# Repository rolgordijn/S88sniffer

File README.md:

# S88NSniffer – Arduino + KiCad

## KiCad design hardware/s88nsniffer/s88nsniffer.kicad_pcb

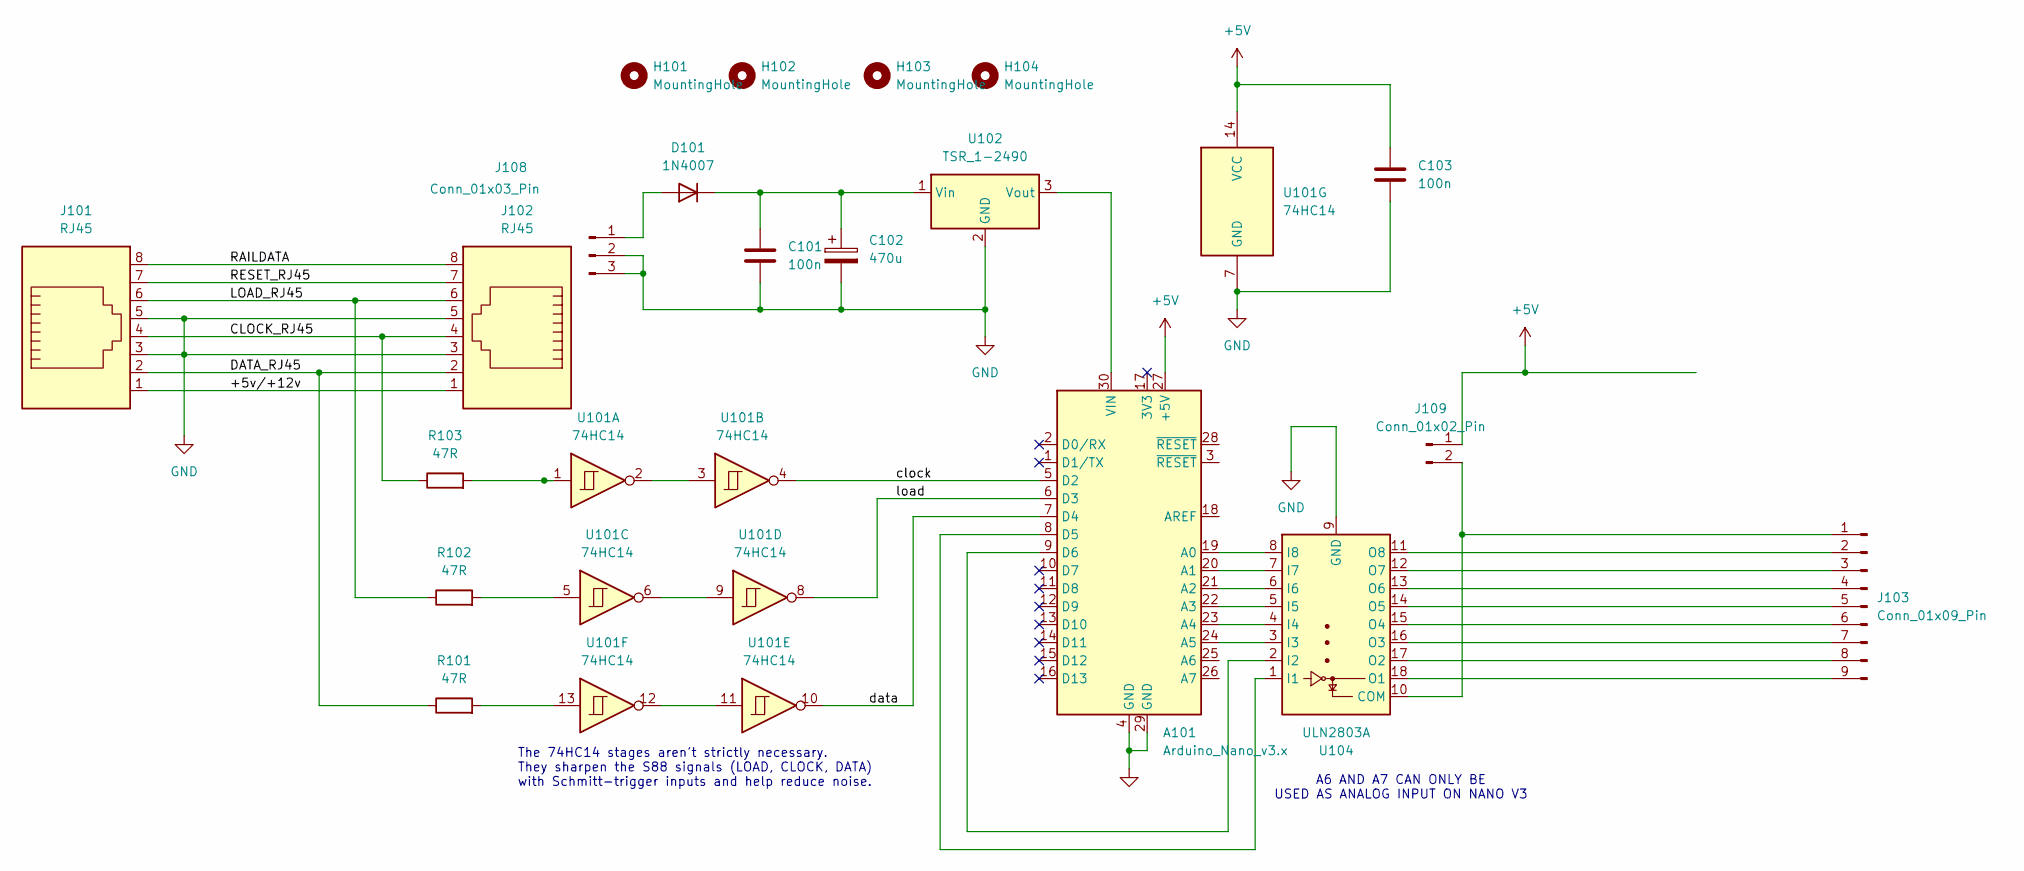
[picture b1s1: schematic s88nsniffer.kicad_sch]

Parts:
A101: Arduino_Nano_v3.x; Arduino_Nano
C101, C103: 100n; C_0805_2012Metric
C102: 470u; CP_Radial_D10.0mm_P3.50mm
D101: 1N4007; D_DO-41_SOD81_P10.16mm_Horizontal
H101, H102, H103, H104: MountingHole; MountingHole_4mm
J101, J102: RJ45; RJ45_Amphenol_RJHSE5380
J103: Conn_01x09_Pin; JST_PH_B9B-PH-K_1x09_P2.00mm_Vertical
J108: Conn_01x03_Pin; JST_PH_B3B-PH-K_1x03_P2.00mm_Vertical
J109: Conn_01x02_Pin; PinHeader_1x02_P2.54mm_Vertical
R101, R102, R103: 47R; C_0805_2012Metric
U101: 74HC14; DIP-14_W7.62mm
U102: TSR_1-2490; Converter_DCDC_TRACO_TSR-1_THT
U104: ULN2803A; DIP-18_W7.62mm

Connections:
+5V: A101.27 (+5V), C103.1, J109.1, U101.14 (VCC)
/+5v/+12v: J101.1, J102.1
/CLOCK_RJ45: J101.4, J102.4, R103.1
/DATA_RJ45: J101.2, J102.2, R101.1
/LOAD_RJ45: J101.6, J102.6, R102.1
/RAILDATA: J101.8, J102.8
/RESET_RJ45: J101.7, J102.7
/clock: A101.5 (D2), U101.4
/data: A101.7 (D4), U101.10
/load: A101.6 (D3), U101.8
GND: A101.4 (GND), A101.29 (GND), C101.2, C102.2, C103.2, J101.3, J101.5, J102.3, J102.5, J108.2, J108.3, U101.7 (GND), U102.2 (GND), U104.9 (GND)
unnamed: A101.19 (A0), U104.8 (I8)
unnamed: A101.20 (A1), U104.7 (I7)
unnamed: A101.21 (A2), U104.6 (I6)
unnamed: A101.22 (A3), U104.5 (I5)
unnamed: A101.23 (A4), U104.4 (I4)
unnamed: A101.24 (A5), U104.3 (I3)
unnamed: A101.8 (D5), U104.1 (I1)
unnamed: A101.9 (D6), U104.2 (I2)
unnamed: A101.30 (VIN), U102.3 (Vout)
unnamed: D101.2 (A), J108.1
unnamed: C101.1, C102.1, D101.1 (K), U102.1 (Vin)
unnamed: J103.1, J109.2, U104.10 (COM)
unnamed: J103.2, U104.11 (O8)
unnamed: J103.3, U104.12 (O7)
unnamed: J103.4, U104.13 (O6)
unnamed: J103.5, U104.14 (O5)
unnamed: J103.6, U104.15 (O4)
unnamed: J103.7, U104.16 (O3)
unnamed: J103.8, U104.17 (O2)
unnamed: J103.9, U104.18 (O1)
unnamed: R101.2, U101.13
unnamed: R102.2, U101.5
unnamed: R103.2, U101.1
unnamed: U101.2, U101.3
unnamed: U101.6, U101.9

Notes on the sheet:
The 74HC14 stages aren't strictly necessary. They sharpen the S88 signals (LOAD, CLOCK, DATA) with Schmitt-trigger inputs and help reduce noise.
A6 AND A7 CAN ONLY BE USED AS ANALOG INPUT ON NANO V3

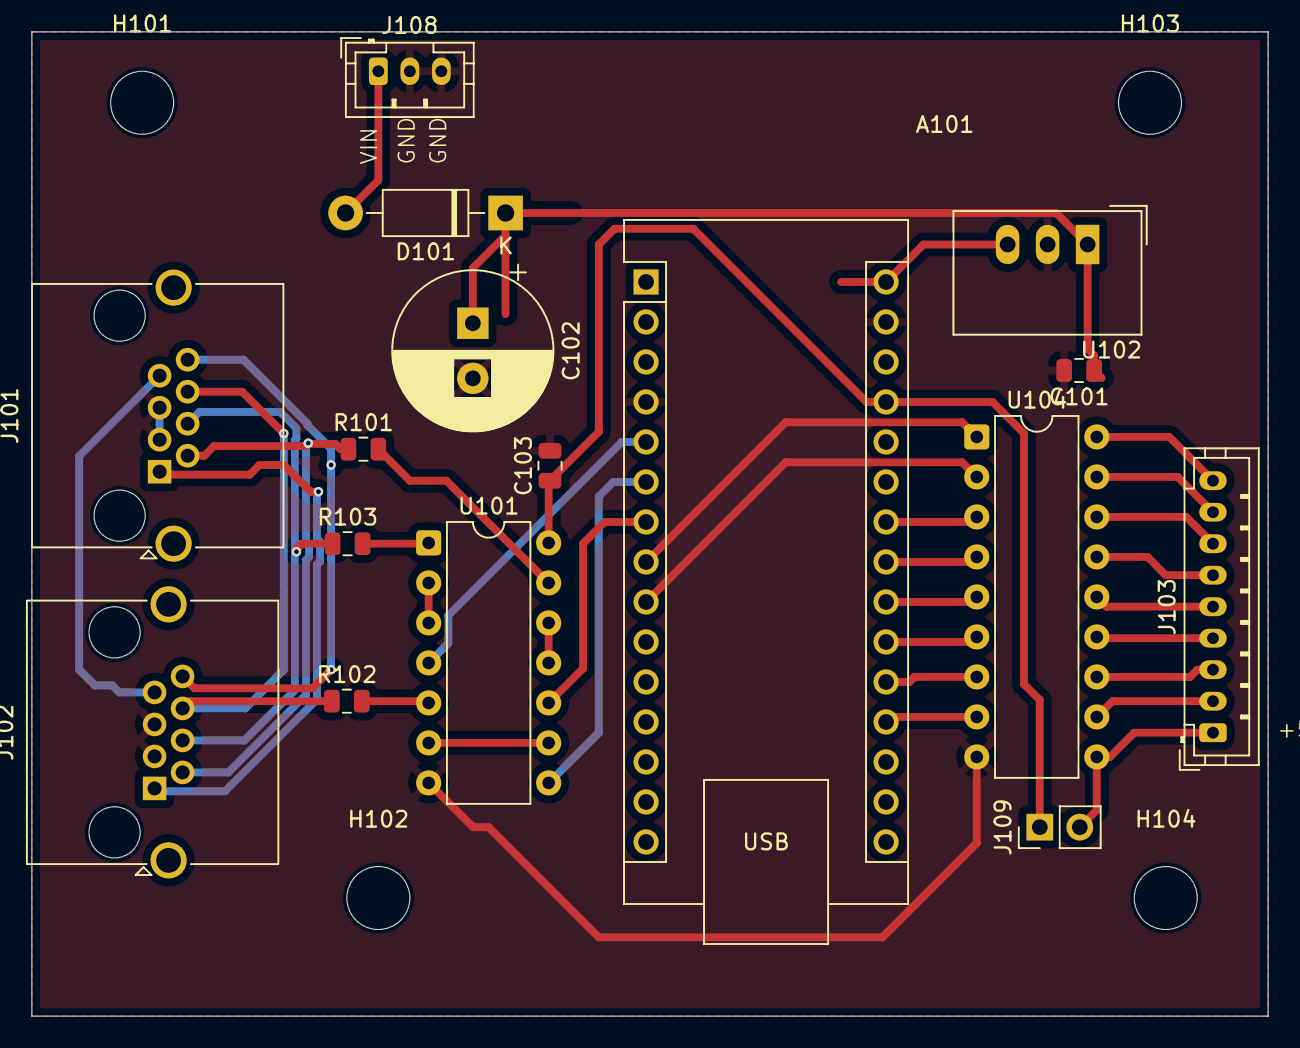
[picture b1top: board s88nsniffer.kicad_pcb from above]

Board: 2 copper layers, 78.5 x 62.5 mm, 20 parts (0 on the bottom side), 36 nets.

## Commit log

2025-10-04 Initial combined project: Arduino + KiCad
2025-10-04 Move README from Arduino folder to project root
2025-10-04 add component values add some info on the schematic fixed a nr of pcb layout issues
2025-10-04 release lock
2025-10-04 BOM details updated
2025-11-08 off by one error? 0,1,2,3 vs counting 1,2,3,4 in arrays...
2025-11-11 interrupt guard
